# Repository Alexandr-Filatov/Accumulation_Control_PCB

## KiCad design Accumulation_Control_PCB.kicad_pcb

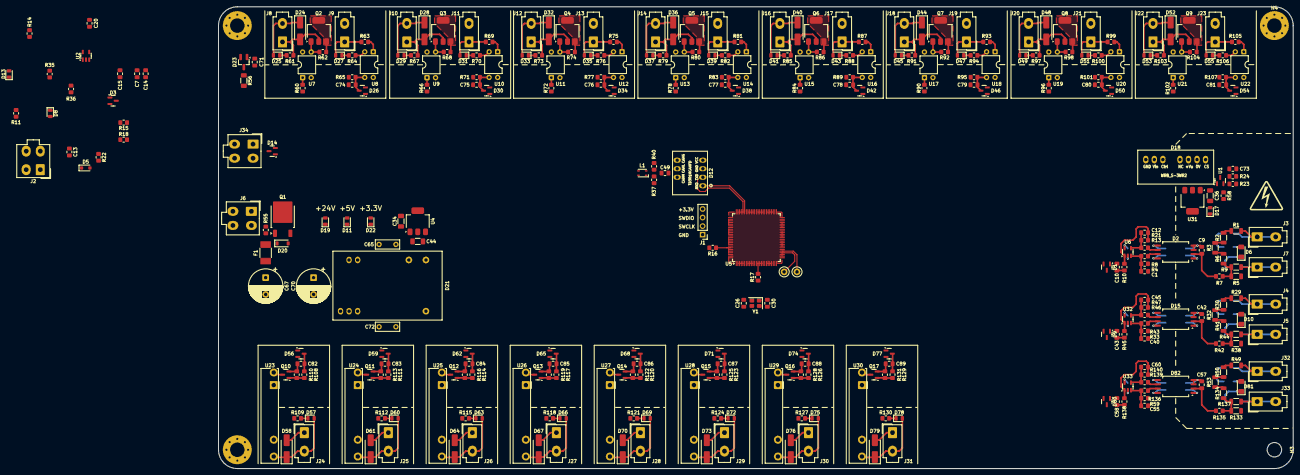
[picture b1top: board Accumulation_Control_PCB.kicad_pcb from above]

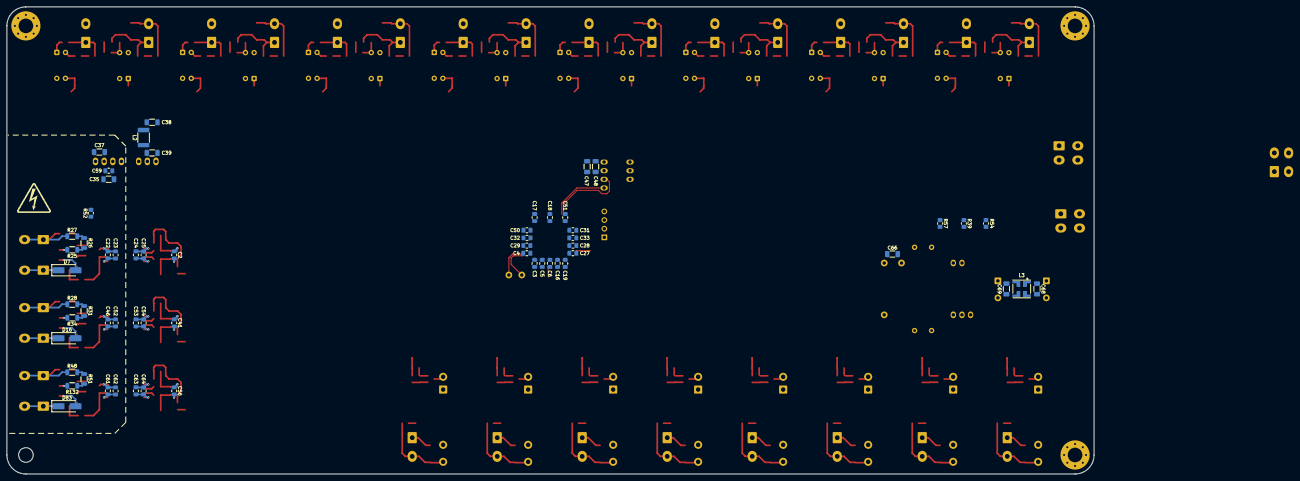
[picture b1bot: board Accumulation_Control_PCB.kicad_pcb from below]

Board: 4 copper layers, 319.7 x 137.4 mm, 399 parts (59 on the bottom side), 202 nets.

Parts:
C1, C9, C12, C15, C40, C42, C45, C55, C57, C60: 56p; C_0805_2012Metric_Pad1.18x1.45mm_HandSolder
C2, C3, C5, C7, C16, C17, C18, C19, C27, C28, C29, C32, C33, C41, C56, C73, C82, C83, C84, C85, C86, C87, C88, C89: 100n; C_0805_2012Metric_Pad1.18x1.45mm_HandSolder
C4, C6, C71, C74, C75, C76, C77, C78, C79, C80, C81: 1u; C_0805_2012Metric_Pad1.18x1.45mm_HandSolder
C10, C20, C43, C58: 0.27u; C_0805_2012Metric_Pad1.18x1.45mm_HandSolder
C13: 47n; C_0805_2012Metric_Pad1.18x1.45mm_HandSolder
C14: 2.2n; C_0805_2012Metric_Pad1.18x1.45mm_HandSolder
C22, C24, C46, C50, C51, C53, C61, C63: 2.2u; C_0805_2012Metric_Pad1.18x1.45mm_HandSolder
C23, C25, C52, C54, C62, C64: 0.1u; C_0805_2012Metric_Pad1.18x1.45mm_HandSolder
C26, C30: 12p; C_0805_2012Metric_Pad1.18x1.45mm_HandSolder
C31: 4.7u; C_0805_2012Metric_Pad1.18x1.45mm_HandSolder
C34, C35, C36, C37, C38, C44, C47, C66, C68, C69: 10u; C_1206_3216Metric_Pad1.33x1.80mm_HandSolder
C39: 1u; C_1206_3216Metric_Pad1.33x1.80mm_HandSolder
C48: 0.1u; C_1206_3216Metric_Pad1.33x1.80mm_HandSolder
C49: 10n; C_0805_2012Metric_Pad1.18x1.45mm_HandSolder
C59: 100u; C_0805_2012Metric_Pad1.18x1.45mm_HandSolder
C65, C72: 1n; C_Disc_D7.0mm_W2.5mm_P5.00mm
C67, C70: 330u; CP_Radial_D10.0mm_P5.00mm
D1, D3, D9, D14, D26, D30, D34, D38, D42, D46, D50, D54, D56, D59, D62, D65, D68, D71, D74, D77, D80: SOT-23
D2, D15, D82: SOIC-8_7.5x5.85mm_P1.27mm
D5: D_SOD-323_HandSoldering
D6, D10, D81: TO-3216BC-MYF; LED_1206_3216Metric_Pad1.42x1.75mm_HandSolder
D7, D16, D83: S1M; D_SMA_Handsoldering
D8, D11, D13, D17, D19, D22, D25, D27, D29, D31, D33, D35, D37, D39, D41, D43, D45, D47, D49, D51, D53, D55, D57, D60, D63, D66, D69, D72, D75, D78: LED_0805_2012Metric
D12: TD301MCANFD; TD5(3)01MCANFD
D18: WRB_S-3WR2
D20: D_SOD-123
D21: URB2405ZP-10WR3; URB_ZP-10WR3
D23: BZX84C5V1; SOT-23_Handsoldering
D24, D28, D32, D36, D40, D44, D48, D52, D58, D61, D64, D67, D70, D73, D76, D79: D_SMA_Handsoldering
F1: 0451002.MRL; SMD_2410
H1, H2, H4: MountingHole_Pad; MountingHole_4.3mm_M4_Pad_Via
H3: MountingHole; MountingHole_4.3mm_M4
J1: PinHeader_1x04_P2.54mm_Vertical
J2, J6, J34: Molex_Mini-Fit_Jr_5566-04A_2x02_P4.20mm_Vertical
J3, J4, J5, J7, J8, J9, J10, J11, J12, J13, J14, J15, J16, J17, J18, J19, J20, J21, J22, J23, J24, J25, J26, J27, J28, J29, J30, J31, J32, J33: Mini-Fit_01x02_Vertical
L1: L_CommonModeChoke_TDK_ACM2520-2P
L2: 4.7u; L_1812_4532Metric_Pad1.30x3.40mm_HandSolder
L3: L_CommonModeChoke_Murata_DLW5BTMxxxSQ2x_5x5mm
Q1: TO-252-2
Q2, Q3, Q4, Q5, Q6, Q7, Q8, Q9: SOT-223
Q10, Q11, Q12, Q13, Q14, Q15, Q16, Q17: SOT-23
R1, R2, R3, R6, R29, R30, R32, R41, R49, R50, R53, R134: 2M; R_1206_3216Metric
R4, R8, R11, R13, R16, R17, R21, R22, R24, R33, R35, R36, R43, R46, R47, R58, R59, R108, R111, R114, R117, R120, R123, R126, R129, R136, R139, R140: 1k; R_0805_2012Metric_Pad1.20x1.40mm_HandSolder
R5, R9, R38, R44, R133, R137: 16k; R_1206_3216Metric
R7, R15, R42, R135: 120; R_0805_2012Metric_Pad1.20x1.40mm_HandSolder
R10, R18, R45, R138: 49.9; R_0805_2012Metric_Pad1.20x1.40mm_HandSolder
R14: 665; R_0805_2012Metric_Pad1.20x1.40mm_HandSolder
R23: 240; R_0805_2012Metric_Pad1.20x1.40mm_HandSolder
R25, R26, R27, R28, R31, R34, R48, R51, R132: 150k; R_1206_3216Metric
R37, R40: 59; R_0805_2012Metric_Pad1.20x1.40mm_HandSolder
R39, R52: 750; R_0805_2012Metric_Pad1.20x1.40mm_HandSolder
R54, R61, R64, R67, R70, R73, R76, R79, R82, R85, R88, R91, R94, R97, R100, R103, R106, R109, R112, R115, R118, R121, R124, R127, R130: 8.2k; R_0805_2012Metric_Pad1.20x1.40mm_HandSolder
R55: 100k; R_0805_2012Metric_Pad1.20x1.40mm_HandSolder
R56: 2.4k; R_1206_3216Metric_Pad1.30x1.75mm_HandSolder
R57: 1.1k; R_0805_2012Metric_Pad1.20x1.40mm_HandSolder
R60, R66, R72, R78, R84, R90, R96, R102: 330; R_0805_2012Metric_Pad1.20x1.40mm_HandSolder
R62, R65, R68, R71, R74, R77, R80, R83, R86, R89, R92, R95, R98, R101, R104, R107, R110, R113, R116, R119, R122, R125, R128, R131: 10k; R_0805_2012Metric_Pad1.20x1.40mm_HandSolder
R63, R69, R75, R81, R87, R93, R99, R105: 3.3k; R_0805_2012Metric_Pad1.20x1.40mm_HandSolder
TP1, TP2: TestPoint; TestPoint_Loop_D1.80mm_Drill1.0mm_Beaded
U1: TLV431; SOT-23
U2, U6, U32, U33: OPA333xxDBV; SOT-23-5
U4, U31: TLV1117LV33DCYR; SOT-223-3_TabPin2
U5: LQFP-100_14x14mm_P0.5mm
U7, U8, U9, U10, U11, U12, U13, U14, U15, U16, U17, U18, U19, U20, U21, U22: PC817; DIP-4_W7.62mm
U23, U24, U25, U26, U27, U28, U29, U30: RSCD06D3; Finder_34.81
Y1: Crystal_SMD_SeikoEpson_FA238-4Pin_3.2x2.5mm

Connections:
+1V0: C73.2, R5.2, R23.2, R24.1, R38.2, R133.2
+3.3V: C2.1, C3.1, C4.1, C5.1, C6.1, C7.1, C16.1, C17.1, C18.1, C19.1, C24.2, C25.1, C27.1, C28.1, C29.1, C31.1, C32.1, C33.1, C34.2, C41.1, C47.1, C48.1, C53.2, C54.1, C56.1, C63.2, C64.1, D1.2 (K), D2.8 (VDD2), D3.2 (K), D5.1 (K), D9.2 (K), D11.2 (A), D12.4 (VCC), D15.8 (VDD2), D26.2 (K), D30.2 (K), D34.2 (K), D38.2 (K), D42.2 (K), D46.2 (K), D50.2 (K), D54.2 (K), D56.2 (K), D59.2 (K), D62.2 (K), D65.2 (K), D68.2 (K), D71.2 (K), D74.2 (K), D77.2 (K), D80.2 (K), D82.8 (VDD2), R17.1, U2.5 (V+), U4.2 (VO), U5.6 (VBAT), U5.11 (VDD), U5.19 (VDD), U5.21 (VREF+), U5.22 (VDDA), U5.28 (VDD), U5.50 (VDD), U5.75 (VDD), U5.100 (VDD), U6.5 (V+), U8.4, U10.4, U12.4, U14.4, U16.4, U18.4, U20.4, U22.4, U32.5 (V+), U33.5 (V+)
+3.3VP: C22.2, C23.1, C36.2, C46.2, C52.1, C61.2, C62.1, D2.1 (VDD1), D15.1 (VDD1), D17.2 (A), D82.1 (VDD1), R58.1, U31.2 (VO)
+5.1V: C71.1, D23.1 (K), R56.1, U7.4, U9.4, U11.4, U13.4, U15.4, U17.4, U19.4, U21.4
+5V: C13.1, C44.2, C65.2, C66.1, D21.14 (+Vo), D22.2 (A), J2.3, R11.2, U4.3 (VI), U23.A1, U24.A1, U25.A1, U26.A1, U27.A1, U28.A1, U29.A1, U30.A1
+24V: C38.1, D19.2 (A), D24.1 (K), D25.2 (A), D28.1 (K), D29.2 (A), D32.1 (K), D33.2 (A), D36.1 (K), D37.2 (A), D40.1 (K), D41.2 (A), D44.1 (K), D45.2 (A), D48.1 (K), D49.2 (A), D52.1 (K), D53.2 (A), F1.1, J6.2, J6.4, J8.2, J9.2, J10.2, J11.2, J12.2, J13.2, J14.2, J15.2, J16.2, J17.2, J18.2, J19.2, J20.2, J21.2, J22.2, J23.2, L2.1, R55.2, R56.2, U23.11, U24.11, U25.11, U26.11, U27.11, U28.11, U29.11, U30.11
-24V: J6.1, J6.3, Q1.2 (D)
/Relay_Control_1/Relay_FeedBack: C74.1, D26.3 (common), R65.1, U8.3
/Relay_Control_2/Relay_FeedBack: C75.1, D30.3 (common), R71.1, U10.3
/Relay_Control_3/Relay_FeedBack: C76.1, D34.3 (common), R77.1, U12.3
/Relay_Control_4/Relay_FeedBack: C77.1, D38.3 (common), R83.1, U14.3
/Relay_Control_5/Relay_FeedBack: C78.1, D42.3 (common), R89.1, U16.3
/Relay_Control_6/Relay_FeedBack: C79.1, D46.3 (common), R95.1, U18.3
/Relay_Control_7/Relay_FeedBack: C80.1, D50.3 (common), R101.1, U20.3
/Relay_Control_8/Relay_FeedBack: C81.1, D54.3 (common), R107.1, U22.3
/Solenoid_control_1/Coil_1_CTRL: C82.1, D56.3 (common), R108.1
/Solenoid_control_2/Coil_1_CTRL: C83.1, D59.3 (common), R111.1
/Solenoid_control_3/Coil_1_CTRL: C84.1, D62.3 (common), R114.1
/Solenoid_control_4/Coil_1_CTRL: C85.1, D65.3 (common), R117.1
/Solenoid_control_5/Coil_1_CTRL: C86.1, D68.3 (common), R120.1
/Solenoid_control_6/Coil_1_CTRL: C87.1, D71.3 (common), R123.1
/Solenoid_control_7/Coil_1_CTRL: C88.1, D74.3 (common), R126.1
/Solenoid_control_8/Coil_1_CTRL: C89.1, D77.3 (common), R129.1
/Voltage_measure_1/VDC_SENSE: C10.1, D1.3 (common), R10.2
/Voltage_measure_2/VDC_SENSE: C43.1, D9.3 (common), R45.2
/Voltage_measure_3/VDC_SENSE: C58.1, D80.3 (common), R138.2
BOOT0: R16.2, U5.94 (BOOT0)
CAN1_RXD_MCU: D12.1 (RXD), U5.70 (PA11)
CAN1_TXD_MCU: D12.2 (TXD), U5.71 (PA12)
CANH: D14.1 (K), J34.2, L1.4
CANL: D14.2 (K), J34.1, L1.3
Crrent_Out: C14.1, J2.1, R11.1, R14.2
Current_SENSE: C20.1, D3.3 (common), R18.2, U5.31 (PA6)
DAC_OUT1: TP1.1, U5.29 (PA4)
DAC_OUT2: TP2.1, U5.30 (PA5)
GND: C1.1, C2.2, C3.2, C4.2, C5.2, C6.2, C7.2, C10.2, C13.2, C14.2, C15.2, C16.2, C17.2, C18.2, C19.2, C20.2, C24.1, C25.2, C26.1, C27.2, C28.2, C29.2, C30.2, C31.2, C32.2, C33.2, C34.1, C38.2, C39.2, C40.1, C41.2, C43.2, C44.1, C47.2, C48.2, C50.2, C51.2, C53.1, C54.2, C55.1, C56.2, C58.2, C63.1, C64.2, C66.2, C72.2, C74.2, C75.2, C76.2, C77.2, C78.2, C79.2, C80.2, C81.2, C82.2, C83.2, C84.2, C85.2, C86.2, C87.2, C88.2, C89.2, D1.1 (A), D2.5 (GND2), D3.1 (A), D9.1 (A), D12.3 (GND), D15.5 (GND2), D18.1 (GND), D21.16 (0V), D26.1 (A), D30.1 (A), D34.1 (A), D38.1 (A), D42.1 (A), D46.1 (A), D50.1 (A), D54.1 (A), D56.1 (A), D59.1 (A), D62.1 (A), D65.1 (A), D68.1 (A), D71.1 (A), D74.1 (A), D77.1 (A), D80.1 (A), D82.5 (GND2), H1.1, H2.1, H4.1, J1.1, J2.2, J2.4, Q10.2 (S), Q11.2 (S), Q12.2 (S), Q13.2 (S), Q14.2 (S), Q15.2 (S), Q16.2 (S), Q17.2 (S), R4.1, R16.1, R22.2, R33.1, R35.2, R36.2, R39.2, R57.2, R59.1, R65.2, R71.2, R77.2, R83.2, R89.2, R95.2, R101.2, R107.2, R110.1, R113.1, R116.1, R119.1, R122.1, R125.1, R128.1, R131.1, U2.2 (V-), U4.1 (GND), U5.10 (VSS), U5.20 (VSSA), U5.27 (VSS), U5.74 (VSS), U5.99 (VSS), U6.2 (V-), U7.2, U9.2, U11.2, U13.2, U15.2, U17.2, U19.2, U21.2, U32.2 (V-), U33.2 (V-), Y1.2, Y1.4
GNDD: C67.2, C68.2, C71.2, D20.2 (A), D23.2 (A), D58.2 (A), D61.2 (A), D64.2 (A), D67.2 (A), D70.2 (A), D73.2 (A), D76.2 (A), D79.2 (A), J24.1, J25.1, J26.1, J27.1, J28.1, J29.1, J30.1, J31.1, L3.4, Q1.3 (S), Q2.3 (S), Q2.4 (S), Q3.3 (S), Q3.4 (S), Q4.3 (S), Q4.4 (S), Q5.3 (S), Q5.4 (S), Q6.3 (S), Q6.4 (S), Q7.3 (S), Q7.4 (S), Q8.3 (S), Q8.4 (S), Q9.3 (S), Q9.4 (S), R54.2, R62.1, R64.2, R68.1, R70.2, R74.1, R76.2, R80.1, R82.2, R86.1, R88.2, R92.1, R94.2, R98.1, R100.2, R104.1, R106.2, R109.2, R112.2, R115.2, R118.2, R121.2, R124.2, R127.2, R130.2, U8.2, U10.2, U12.2, U14.2, U16.2, U18.2, U20.2, U22.2
GNDPWR: C9.2, C22.1, C23.2, C35.1, C36.1, C37.1, C42.2, C46.1, C52.2, C57.2, C59.2, C61.1, C62.2, C73.1, D2.3 (SHTDN), D2.4 (GND1), D7.1 (K), D15.3 (SHTDN), D15.4 (GND1), D16.1 (K), D18.7 (0V), D82.3 (SHTDN), D82.4 (GND1), D83.1 (K), J5.1, J5.2, J7.1, J7.2, J33.1, J33.2, R9.1, R24.2, R44.1, R52.2, R137.1, U1.3 (A), U31.1 (GND)
GND_CAN: C49.2, D12.5 (CANG), D14.3 (A), J34.3, J34.4
NRST: R17.2, U5.14 (NRST)
unnamed: C12.2, R10.1, R21.2, U6.1
unnamed: C45.2, R45.1, R47.2, U32.1
unnamed: C49.1, R37.1, R40.2
unnamed: C60.2, R138.1, R140.2, U33.1
unnamed: C65.1, C69.1, C70.1, D21.22 (Vin), D21.23 (Vin), L3.2
unnamed: C67.1, C68.1, F1.2, L3.1
unnamed: C69.2, C70.2, C72.1, D21.2 (GND), D21.3 (GND), L3.3
unnamed: D2.6 (OUTN), R13.1
unnamed: D2.7 (OUTP), R8.1
unnamed: C9.1, D2.2 (VIN), R7.1
unnamed: D5.2 (A), J1.4
unnamed: D6.2 (A), R25.2
unnamed: D6.1 (K), D7.2 (A)
unnamed: D8.2 (A), U5.52 (PB13)
unnamed: D8.1 (K), R35.1
unnamed: D10.2 (A), R34.2
unnamed: D10.1 (K), D16.2 (A)
unnamed: D11.1 (K), R39.1
unnamed: D12.7 (CANH), L1.1, R37.2
unnamed: D12.6 (CANL), L1.2, R40.1
unnamed: D13.2 (A), U5.57 (PD10)
unnamed: D13.1 (K), R36.1
unnamed: D15.6 (OUTN), R46.1
unnamed: D15.7 (OUTP), R43.1
unnamed: C42.1, D15.2 (VIN), R42.1
unnamed: D17.1 (K), R52.1
unnamed: C35.2, C59.1, D18.6 (+Vo), U31.3 (VI)
unnamed: C37.2, D18.8 (CS)
unnamed: C39.1, D18.2 (Vin), L2.2
unnamed: D19.1 (K), R54.1
unnamed: D20.1 (K), Q1.1 (G), R55.1
unnamed: D22.1 (K), R57.1
unnamed: D24.2 (A), J8.1, Q2.2 (D), R61.2
unnamed: D25.1 (K), R61.1
unnamed: D27.2 (A), J9.1, R63.2
unnamed: D27.1 (K), R64.1
unnamed: D28.2 (A), J10.1, Q3.2 (D), R67.2
unnamed: D29.1 (K), R67.1
unnamed: D31.2 (A), J11.1, R69.2
unnamed: D31.1 (K), R70.1
unnamed: D32.2 (A), J12.1, Q4.2 (D), R73.2
unnamed: D33.1 (K), R73.1
unnamed: D35.2 (A), J13.1, R75.2
unnamed: D35.1 (K), R76.1
unnamed: D36.2 (A), J14.1, Q5.2 (D), R79.2
unnamed: D37.1 (K), R79.1
unnamed: D39.2 (A), J15.1, R81.2
unnamed: D39.1 (K), R82.1
unnamed: D40.2 (A), J16.1, Q6.2 (D), R85.2
unnamed: D41.1 (K), R85.1
unnamed: D43.2 (A), J17.1, R87.2
unnamed: D43.1 (K), R88.1
unnamed: D44.2 (A), J18.1, Q7.2 (D), R91.2
unnamed: D45.1 (K), R91.1
unnamed: D47.2 (A), J19.1, R93.2
unnamed: D47.1 (K), R94.1
unnamed: D48.2 (A), J20.1, Q8.2 (D), R97.2
unnamed: D49.1 (K), R97.1
unnamed: D51.2 (A), J21.1, R99.2
unnamed: D51.1 (K), R100.1
unnamed: D52.2 (A), J22.1, Q9.2 (D), R103.2
unnamed: D53.1 (K), R103.1
unnamed: D55.2 (A), J23.1, R105.2
unnamed: D55.1 (K), R106.1
unnamed: D57.2 (A), D58.1 (K), J24.2, U23.14
unnamed: D57.1 (K), R109.1
unnamed: D60.2 (A), D61.1 (K), J25.2, U24.14
unnamed: D60.1 (K), R112.1
unnamed: D63.2 (A), D64.1 (K), J26.2, U25.14
unnamed: D63.1 (K), R115.1
unnamed: D66.2 (A), D67.1 (K), J27.2, U26.14
unnamed: D66.1 (K), R118.1
unnamed: D69.2 (A), D70.1 (K), J28.2, U27.14
unnamed: D69.1 (K), R121.1
unnamed: D72.2 (A), D73.1 (K), J29.2, U28.14
unnamed: D72.1 (K), R124.1
unnamed: D75.2 (A), D76.1 (K), J30.2, U29.14
unnamed: D75.1 (K), R127.1
unnamed: D78.2 (A), D79.1 (K), J31.2, U30.14
unnamed: D78.1 (K), R130.1
unnamed: D81.2 (A), R132.2
unnamed: D81.1 (K), D83.2 (A)
unnamed: D82.6 (OUTN), R139.1
unnamed: D82.7 (OUTP), R136.1
unnamed: C57.1, D82.2 (VIN), R135.1
unnamed: J1.2, U5.76 (PA14)
unnamed: J1.3, U5.72 (PA13)
unnamed: J3.1, J3.2, R1.2, R27.1
unnamed: J4.1, J4.2, R28.1, R29.2
unnamed: J32.1, J32.2, R48.1, R49.2
unnamed: Q2.1 (G), R62.2, U7.3
unnamed: Q3.1 (G), R68.2, U9.3
unnamed: Q4.1 (G), R74.2, U11.3
unnamed: Q5.1 (G), R80.2, U13.3
unnamed: Q6.1 (G), R86.2, U15.3
unnamed: Q7.1 (G), R92.2, U17.3
unnamed: Q8.1 (G), R98.2, U19.3
unnamed: Q9.1 (G), R104.2, U21.3
unnamed: Q10.3 (D), U23.A2
unnamed: Q10.1 (G), R108.2, R110.2
unnamed: Q11.3 (D), U24.A2
unnamed: Q11.1 (G), R111.2, R113.2
unnamed: Q12.3 (D), U25.A2
unnamed: Q12.1 (G), R114.2, R116.2
unnamed: Q13.3 (D), U26.A2
unnamed: Q13.1 (G), R117.2, R119.2
unnamed: Q14.3 (D), U27.A2
unnamed: Q14.1 (G), R120.2, R122.2
unnamed: Q15.3 (D), U28.A2
unnamed: Q15.1 (G), R123.2, R125.2
unnamed: Q16.3 (D), U29.A2
unnamed: Q16.1 (G), R126.2, R128.2
unnamed: Q17.3 (D), U30.A2
unnamed: Q17.1 (G), R129.2, R131.2
unnamed: R1.1, R2.2
unnamed: R2.1, R3.2
unnamed: R3.1, R6.2
unnamed: R5.1, R6.1, R7.2, R9.2
unnamed: R14.1, R15.1, R22.1
unnamed: R25.1, R26.2
unnamed: R26.1, R27.2
unnamed: R28.2, R31.1
unnamed: R29.1, R30.2
unnamed: R30.1, R32.2
unnamed: R31.2, R34.1
unnamed: R32.1, R41.2
unnamed: R38.1, R41.1, R42.2, R44.2
unnamed: R48.2, R51.1
unnamed: R49.1, R50.2
unnamed: R50.1, R53.2
unnamed: R60.2, U7.1
unnamed: R63.1, U8.1
unnamed: R66.2, U9.1
unnamed: R69.1, U10.1
unnamed: R72.2, U11.1
unnamed: R75.1, U12.1
unnamed: R78.2, U13.1
unnamed: R81.1, U14.1
unnamed: R84.2, U15.1
unnamed: R87.1, U16.1
unnamed: R90.2, U17.1
unnamed: R93.1, U18.1
unnamed: R96.2, U19.1
unnamed: R99.1, U20.1
unnamed: R102.2, U21.1
unnamed: R105.1, U22.1
unnamed: R51.2, R132.1
unnamed: R133.1, R134.1, R135.2, R137.2
unnamed: R53.1, R134.2
unnamed: R23.1, R58.2, U1.1 (K), U1.2 (REF)
unnamed: C15.1, R15.2, U2.3 (+)
unnamed: R18.1, U2.1, U2.4 (-)
unnamed: C26.2, U5.12 (PH0), Y1.3
unnamed: C30.1, U5.13 (PH1), Y1.1
unnamed: C50.1, U5.49 (VCAP_1)
unnamed: C51.1, U5.73 (VCAP_2)
unnamed: C1.2, R4.2, R8.2, U6.3 (+)
unnamed: C12.1, R13.2, R21.1, U6.4 (-)
unnamed: C40.2, R33.2, R43.2, U32.3 (+)
unnamed: C45.1, R46.2, R47.1, U32.4 (-)
unnamed: C55.2, R59.2, R136.2, U33.3 (+)
unnamed: C60.1, R139.2, R140.1, U33.4 (-)

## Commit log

2026-03-25 zero commit
2026-03-25 VER1.0: добавил один канал управления клапаном
2026-03-27 VER1.0: размножил на 8 каналов всего, отвязал 24Въ
2026-03-30 VER1.0: изолировал питание 5В и CAN
2026-03-31 VER1.0: разместил все 8 каналов управления
2026-04-01 VER1.0: улучшил и расставил каналы измерения напряжения
2026-04-22 VER1.0: убрал лишнюю шелкографию
